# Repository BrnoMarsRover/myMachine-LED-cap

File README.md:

# myMachine-LED-cap
Repository for my Machine LED Cap project, including software, PCBs, and documentation.

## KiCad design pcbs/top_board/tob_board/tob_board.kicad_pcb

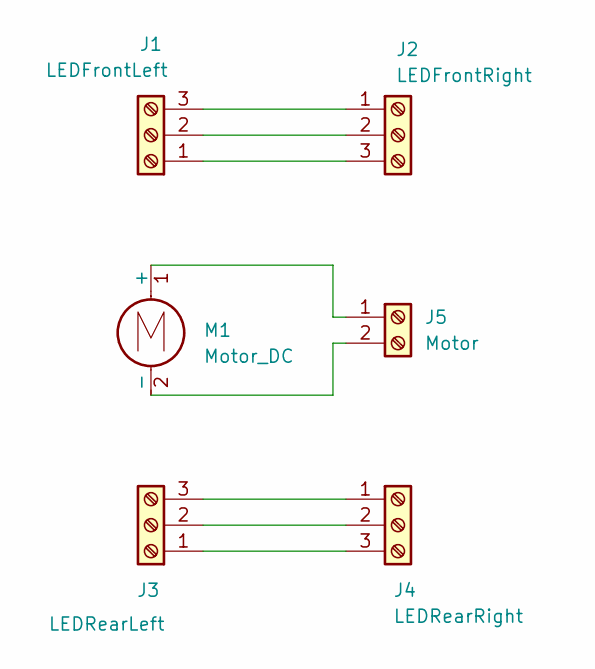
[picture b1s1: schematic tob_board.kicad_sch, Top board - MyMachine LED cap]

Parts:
J1: LEDFrontLeft; JST_XH_S3B-XH-A_1x03_P2.50mm_Horizontal; Manufacturer Part Number S3B-XH-A-1 (LF)(SN)
J2: LEDFrontRight; JST_XH_S3B-XH-A_1x03_P2.50mm_Horizontal; Manufacturer Part Number S3B-XH-A-1 (LF)(SN)
J3: LEDRearLeft; JST_XH_S3B-XH-A_1x03_P2.50mm_Horizontal; Manufacturer Part Number S3B-XH-A-1 (LF)(SN)
J4: LEDRearRight; JST_XH_S3B-XH-A_1x03_P2.50mm_Horizontal; Manufacturer Part Number S3B-XH-A-1 (LF)(SN)
J5: Motor; JST_XH_S2B-XH-A_1x02_P2.50mm_Horizontal; Manufacturer Part Number S2B-XH-A-BK(LF)(SN)
M1: Motor_DC; topMotor; Manufacturer Part Number LA143024A

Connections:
unnamed: J1.1, J2.3
unnamed: J1.2, J2.2
unnamed: J1.3, J2.1
unnamed: J3.1, J4.3
unnamed: J3.2, J4.2
unnamed: J3.3, J4.1
unnamed: J5.1, M1.1 (+)
unnamed: J5.2, M1.2 (-)

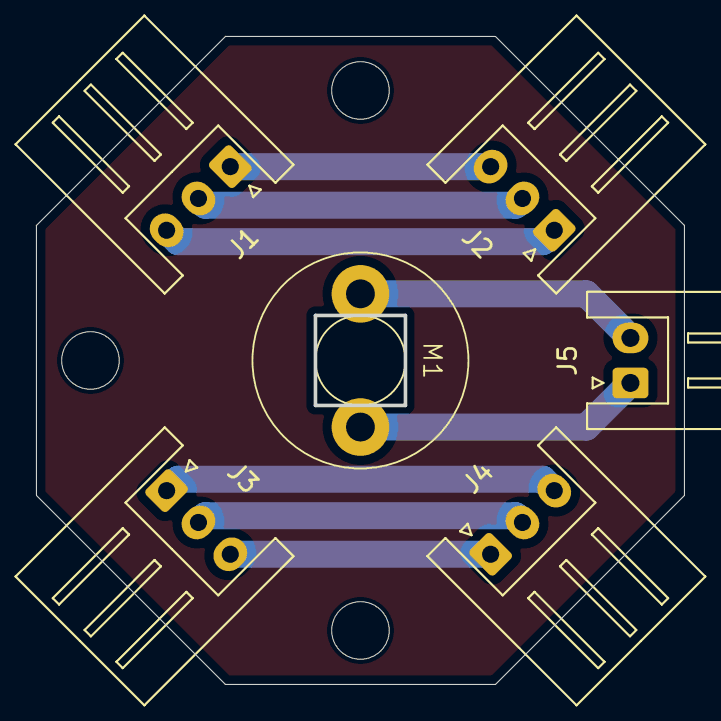
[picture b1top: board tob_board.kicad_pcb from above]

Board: 2 copper layers, 36.0 x 36.0 mm, 6 parts (0 on the bottom side), 8 nets.

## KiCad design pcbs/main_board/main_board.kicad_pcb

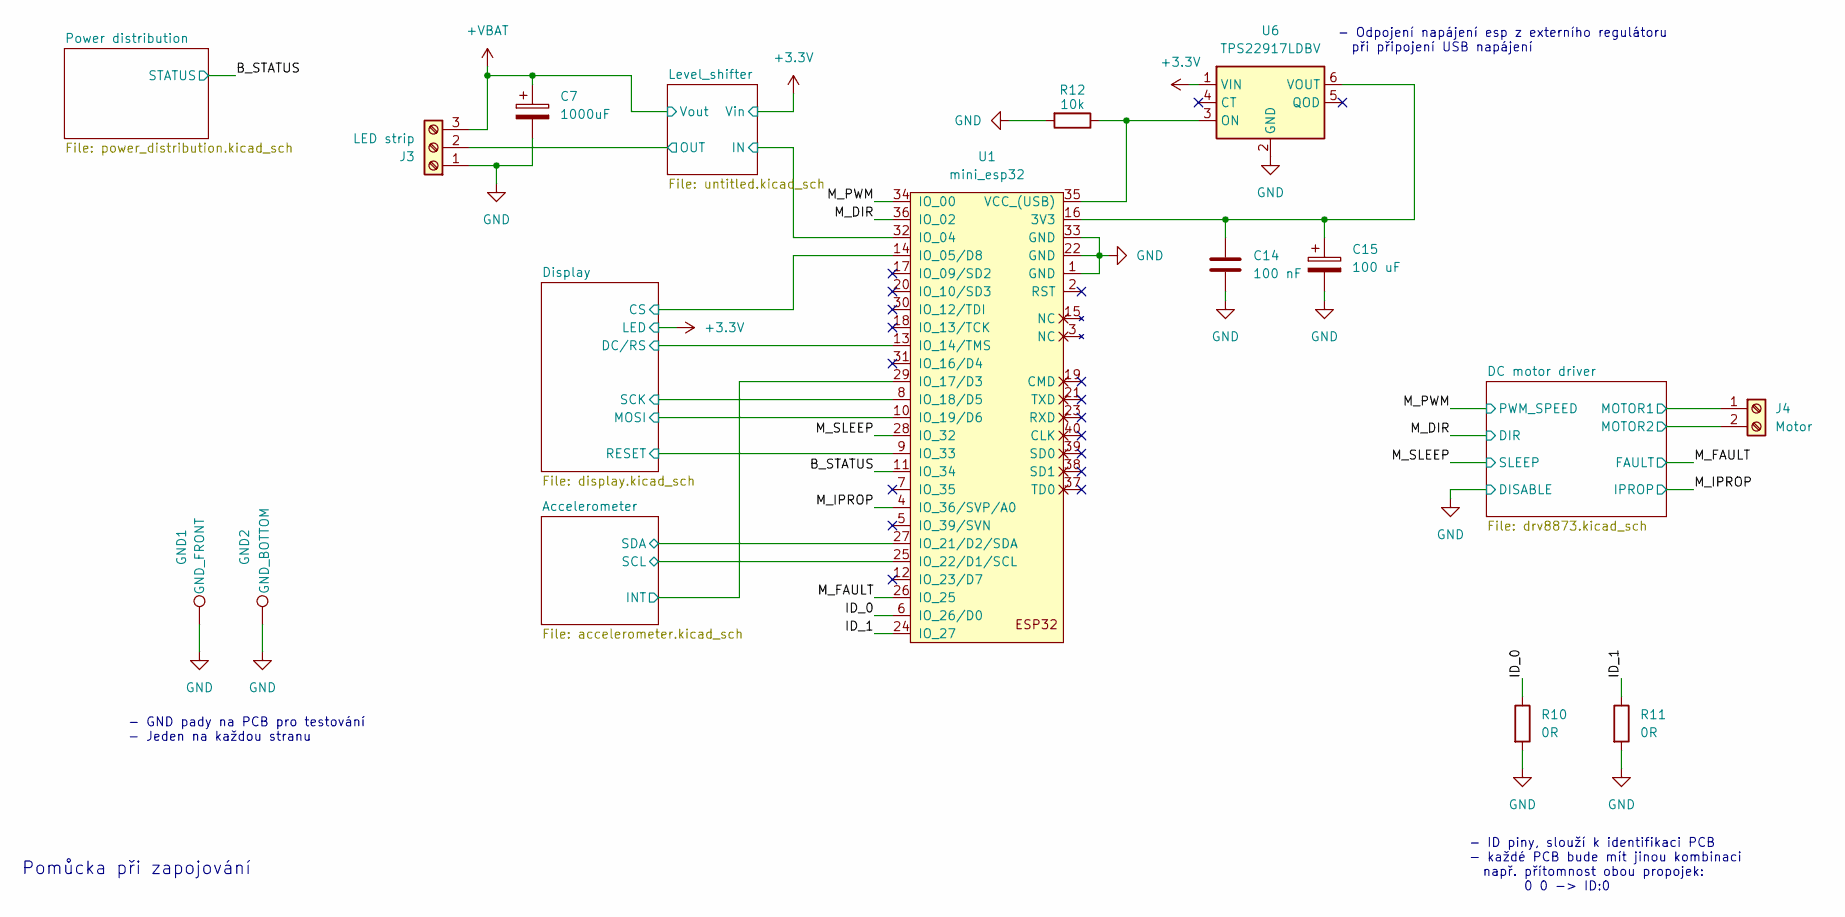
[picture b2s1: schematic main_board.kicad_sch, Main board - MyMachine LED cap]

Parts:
C7: 1000uF; CP_EIA-7360-38_Kemet-E_HandSolder; Manufacturer Part Number TCN4108M006R0055
C14: 100 nF; C_0603_1608Metric_Pad1.08x0.95mm_HandSolder; Manufacturer Part Number C0603C104M5RACTU
C15: 100 uF; CP_EIA-7343-40_Kemet-Y_HandSolder; Manufacturer Part Number T491X107K016AT7280
GND1: GND_FRONT; TestPoint_Pad_1.5x1.5mm
GND2: GND_BOTTOM; TestPoint_Pad_1.5x1.5mm
J3: LED strip; JST_XH_S3B-XH-A-1_1x03_P2.50mm_Horizontal; Manufacturer Part Number S3B-XH-A-1 (LF)(SN)
J4: Motor; JST_XH_S2B-XH-A-1_1x02_P2.50mm_Horizontal; Manufacturer Part Number S2B-XH-A-BK(LF)(SN)
R10, R11: 0R; R_0603_1608Metric_Pad0.98x0.95mm_HandSolder; Manufacturer Part Number CRCW06030000Z0EI
R12: 10k; R_0603_1608Metric_Pad0.98x0.95mm_HandSolder; Manufacturer Part Number CRCW060310K0FKEI
U1: mini_esp32; ESP32_mini; Manufacturer Part Number LA100089
U6: TPS22917LDBV; SOT-23-6; Manufacturer Part Number TPS22917LDBVR

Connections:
+3.3V: U6.1 (VIN); also elsewhere on the board
+VBAT: C7.1, J3.3; also elsewhere on the board
/Accelerometer/INT: U1.29 (IO_17/D3); also elsewhere on the board
/Accelerometer/SCL: U1.25 (IO_22/D1/SCL); also elsewhere on the board
/Accelerometer/SDA: U1.27 (IO_21/D2/SDA); also elsewhere on the board
/B_STATUS: U1.11 (IO_34); also elsewhere on the board
/DC motor driver/MOTOR1: J4.1; also elsewhere on the board
/DC motor driver/MOTOR2: J4.2; also elsewhere on the board
/Display/CS: U1.14 (IO_05/D8); also elsewhere on the board
/Display/DC/RS: U1.13 (IO_14/TMS); also elsewhere on the board
/Display/MOSI: U1.10 (IO_19/D6); also elsewhere on the board
/Display/RESET: U1.9 (IO_33); also elsewhere on the board
/Display/SCK: U1.8 (IO_18/D5); also elsewhere on the board
/ID_0: R10.1, U1.6 (IO_26/D0)
/ID_1: R11.1, U1.24 (IO_27)
/Level_shifter/IN: U1.32 (IO_04); also elsewhere on the board
/Level_shifter/OUT: J3.2; also elsewhere on the board
/M_DIR: U1.36 (IO_02); also elsewhere on the board
/M_FAULT: U1.26 (IO_25); also elsewhere on the board
/M_IPROP: U1.4 (IO_36/SVP/A0); also elsewhere on the board
/M_PWM: U1.34 (IO_00); also elsewhere on the board
/M_SLEEP: U1.28 (IO_32); also elsewhere on the board
GND: C7.2, C14.2, C15.2, GND1.1, GND2.1, J3.1, R10.2, R11.2, R12.2, U1.1 (GND), U1.22 (GND), U1.33 (GND), U6.2 (GND); also elsewhere on the board
unnamed: C14.1, C15.1, U1.16 (3V3), U6.6 (VOUT)
unnamed: R12.1, U1.35 (VCC_(USB)), U6.3 (ON)

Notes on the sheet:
Pomůcka při zapojování
- Odpojení napájení esp z externího regulátoru při připojení USB napájení
- ID piny, slouží k identifikaci PCB - každé PCB bude mít jinou kombinaci např. přítomnost obou propojek: 0 0 -> ID:0
- GND pady na PCB pro testování - Jeden na každou stranu

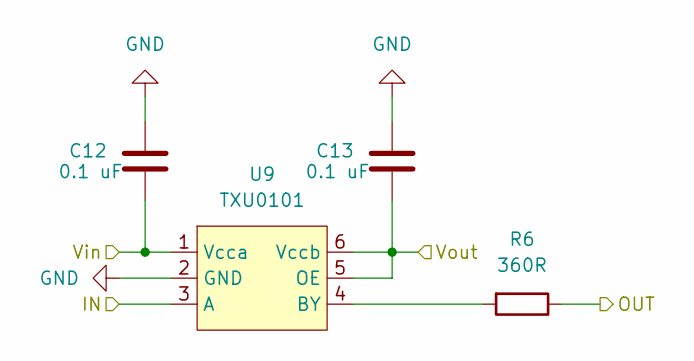
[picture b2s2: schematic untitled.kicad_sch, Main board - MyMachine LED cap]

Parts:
C12, C13: 0.1 uF; C_0603_1608Metric_Pad1.08x0.95mm_HandSolder; Manufacturer Part Number CC0603JRX7R9BB104
R6: 360R; R_0603_1608Metric_Pad0.98x0.95mm_HandSolder; Manufacturer Part Number CRCW0603360RJNTA
U9: TXU0101; SOT-363_SC-70-6_Handsoldering; Manufacturer Part Number TXU0101DCKR

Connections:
+3.3V: C12.1, U9.1 (Vcca); also elsewhere on the board
+VBAT: C13.1, U9.5 (OE), U9.6 (Vccb); also elsewhere on the board
/Level_shifter/IN: U9.3 (A); also elsewhere on the board
/Level_shifter/OUT: R6.1; also elsewhere on the board
GND: C12.2, C13.2, U9.2 (GND); also elsewhere on the board
unnamed: R6.2, U9.4 (BY)

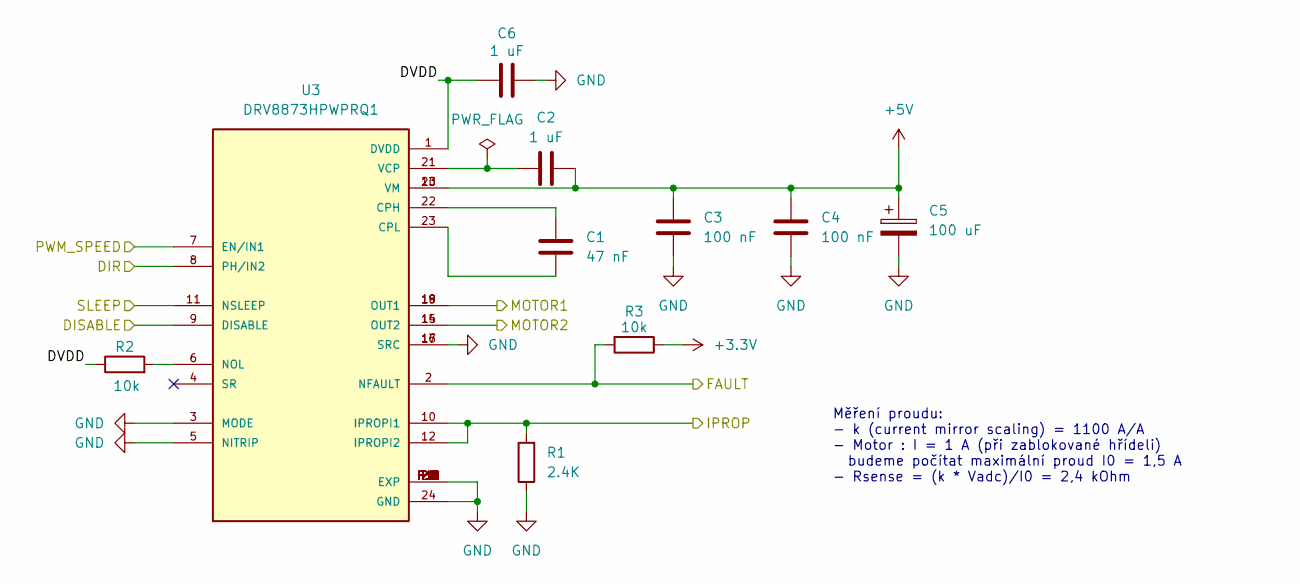
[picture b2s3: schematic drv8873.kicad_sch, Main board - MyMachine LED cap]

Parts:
C1: 47 nF; C_0603_1608Metric_Pad1.08x0.95mm_HandSolder; Manufacturer Part Number CC0603ZRY5V9BB473
C2, C6: 1 uF; C_0603_1608Metric_Pad1.08x0.95mm_HandSolder; Manufacturer Part Number CC0603KRX5R6BB105
C3, C4: 100 nF; C_0603_1608Metric_Pad1.08x0.95mm_HandSolder; Manufacturer Part Number C0603C104M5RACTU
C5: 100 uF; CP_EIA-7343-40_Kemet-Y_HandSolder; Manufacturer Part Number T491X107K016AT7280
R1: 2.4K; R_0603_1608Metric_Pad0.98x0.95mm_HandSolder; Manufacturer Part Number AR0603JR-072K4L
R2, R3: 10k; R_0603_1608Metric_Pad0.98x0.95mm_HandSolder; Manufacturer Part Number CRCW060310K0FKEI
U3: DRV8873HPWPRQ1; SOP65P640X120-25N; Manufacturer Part Number DRV8873HPWPR

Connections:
+3.3V: R3.1; also elsewhere on the board
+5V: C2.2, C3.1, C4.1, C5.1, U3.13 (VM), U3.20 (VM); also elsewhere on the board
/DC motor driver/DVDD: C6.1, R2.1, U3.1 (DVDD)
/DC motor driver/MOTOR1: U3.18 (OUT1), U3.19 (OUT1); also elsewhere on the board
/DC motor driver/MOTOR2: U3.14 (OUT2), U3.15 (OUT2); also elsewhere on the board
/M_DIR: U3.8 (PH/IN2); also elsewhere on the board
/M_FAULT: R3.2, U3.2 (NFAULT); also elsewhere on the board
/M_IPROP: R1.2, U3.10 (IPROPI1), U3.12 (IPROPI2); also elsewhere on the board
/M_PWM: U3.7 (EN/IN1); also elsewhere on the board
/M_SLEEP: U3.11 (NSLEEP); also elsewhere on the board
GND: C3.2, C4.2, C5.2, C6.2, R1.1, U3.3 (MODE), U3.5 (NITRIP), U3.9 (DISABLE), U3.16 (SRC), U3.17 (SRC), U3.24 (GND), U3.25 (EXP), U3.P1 (EXP), U3.P2 (EXP), U3.P3 (EXP), U3.P4 (EXP), U3.P5 (EXP), U3.P6 (EXP), U3.P7 (EXP), U3.P8 (EXP), U3.P9 (EXP), U3.P10 (EXP), U3.P11 (EXP), U3.P12 (EXP), U3.P13 (EXP), U3.P14 (EXP), U3.P15 (EXP), U3.P16 (EXP), U3.P17 (EXP), U3.P18 (EXP); also elsewhere on the board
unnamed: C1.1, U3.22 (CPH)
unnamed: C1.2, U3.23 (CPL)
unnamed: R2.2, U3.6 (NOL)
unnamed: C2.1, U3.21 (VCP)

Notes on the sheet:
Měření proudu: - k (current mirror scaling) = 1100 A/A - Motor : I = 1 A (při zablokované hřídeli) budeme počítat maximální proud I0 = 1,5 A - Rsense = (k * Vadc)/I0 = 2,4 kOhm

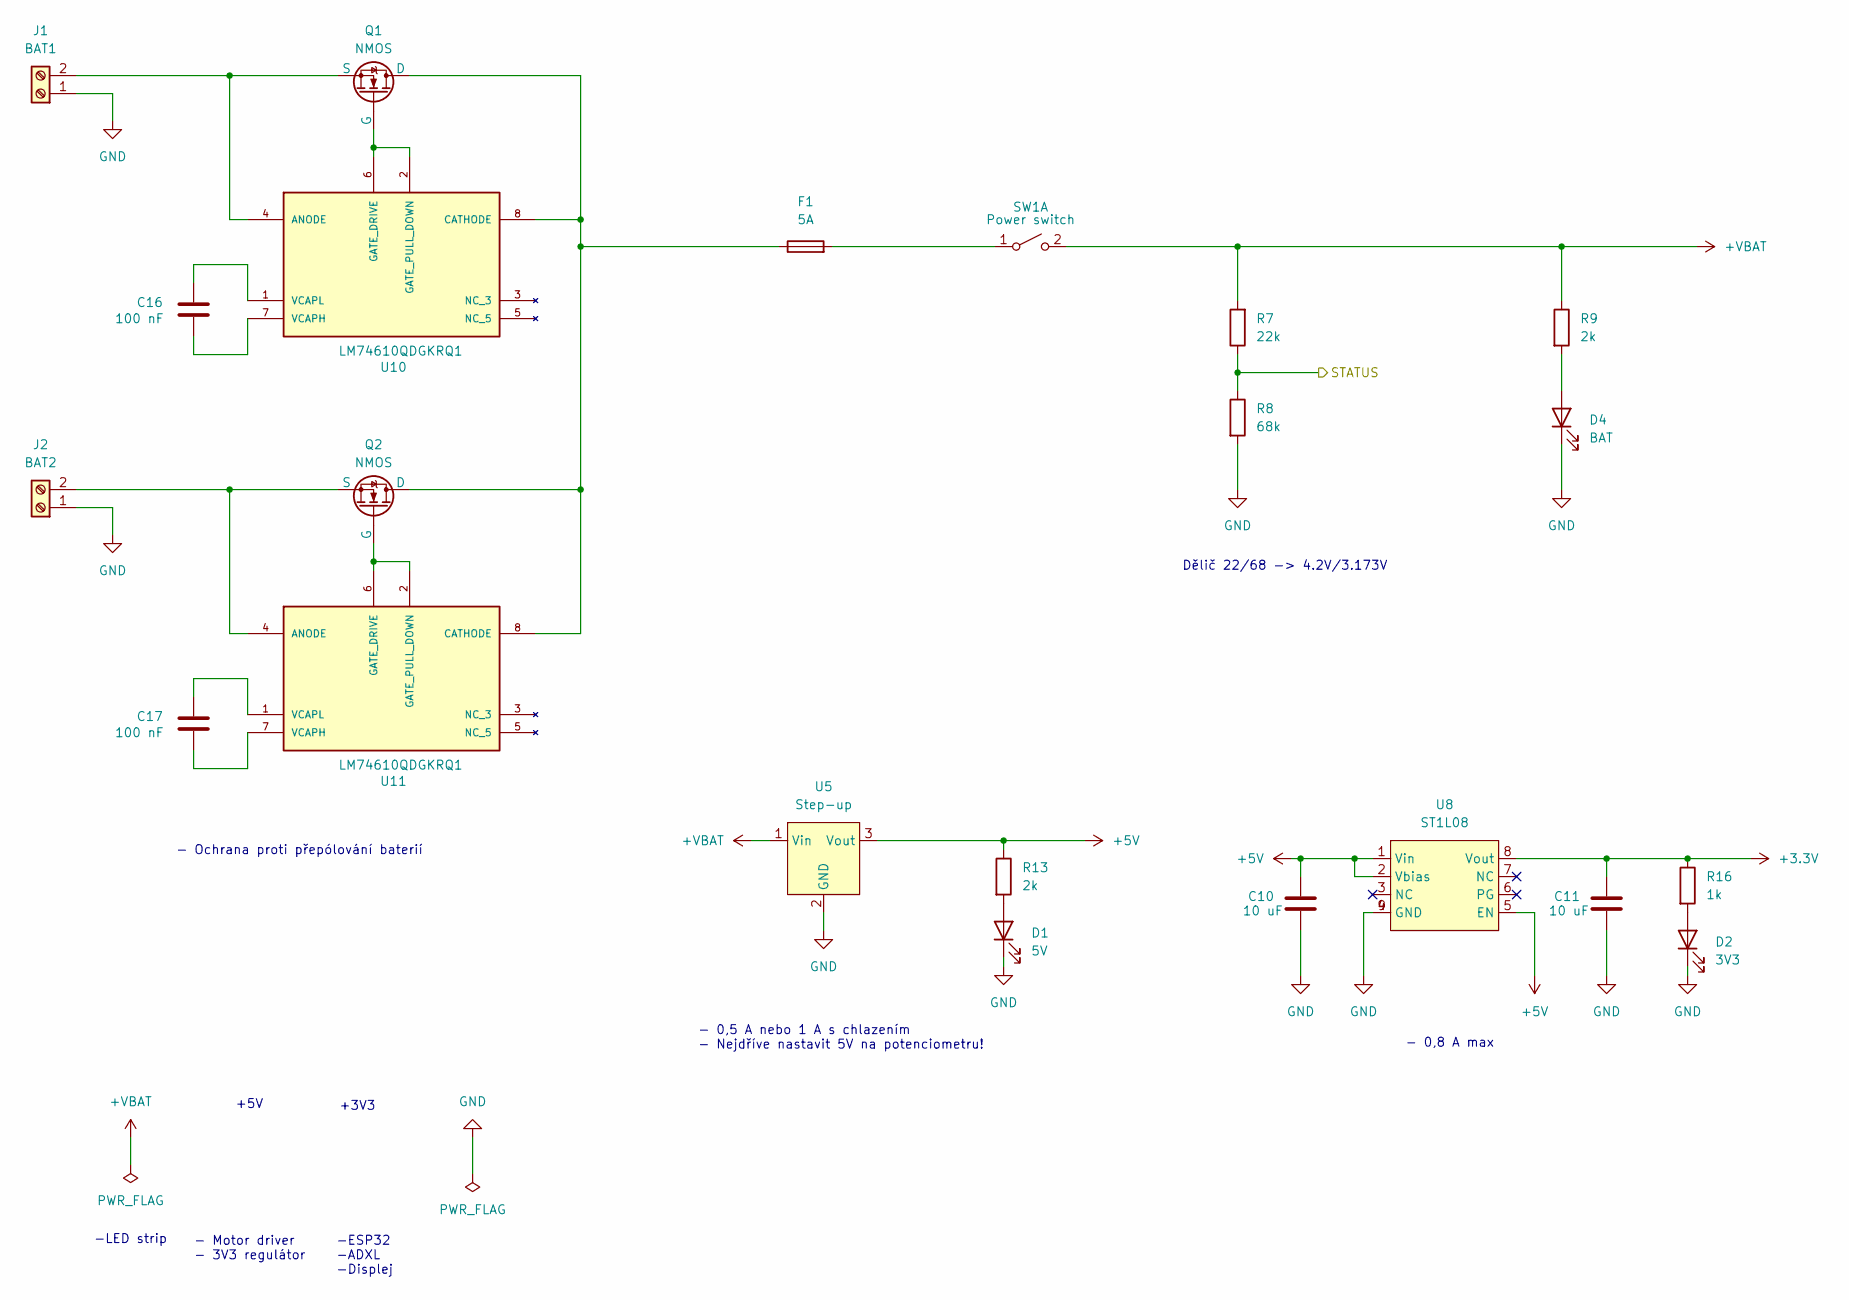
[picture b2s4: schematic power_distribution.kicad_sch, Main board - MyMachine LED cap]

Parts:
C10, C11: 10 uF; C_0603_1608Metric_Pad1.08x0.95mm_HandSolder; Manufacturer Part Number C0603C106M8PAC7411
C16, C17: 100 nF; C_0603_1608Metric_Pad1.08x0.95mm_HandSolder; Manufacturer Part Number C0603C104M5RACTU
D1: 5V; LED_0805_2012Metric_Pad1.15x1.40mm_HandSolder; Manufacturer Part Number APTD2012LCGCK
D2: 3V3; LED_0805_2012Metric_Pad1.15x1.40mm_HandSolder; Manufacturer Part Number APTD2012LCGCK
D4: BAT; LED_0805_2012Metric_Pad1.15x1.40mm_HandSolder; Manufacturer Part Number APTD2012LCGCK
F1: 5A; Fuse_0603_1608Metric_Pad1.05x0.95mm_HandSolder; Manufacturer Part Number SF-0603F500-2
J1: BAT1; JST_XH_S2B-XH-A-1_1x02_P2.50mm_Horizontal; Manufacturer Part Number S2B-XH-A-BK(LF)(SN)
J2: BAT2; JST_XH_S2B-XH-A-1_1x02_P2.50mm_Horizontal; Manufacturer Part Number S2B-XH-A-BK(LF)(SN)
Q1, Q2: NMOS; SO-8_3.9x4.9mm_P1.27mm; Manufacturer Part Number IRF8714TRPBFXTMA1
R7: 22k; R_0603_1608Metric_Pad0.98x0.95mm_HandSolder; Manufacturer Part Number CRCW060322K0FKEBC
R8: 68k; R_0603_1608Metric_Pad0.98x0.95mm_HandSolder; Manufacturer Part Number CRCW060368K0FKTA
R9, R13: 2k; R_0603_1608Metric_Pad0.98x0.95mm_HandSolder; Manufacturer Part Number AR0603FR-072KL
R16: 1k; R_0603_1608Metric_Pad0.98x0.95mm_HandSolder; Manufacturer Part Number RC0603FR-071KL
SW1: Power switch; JST_XH_S2B-XH-A-1_1x02_P2.50mm_Horizontal; Manufacturer Part Number S2B-XH-A-BK(LF)(SN)
U5: Step-up; step-up_module; Manufacturer Part Number LA122015
U8: ST1L08; DFN-8-1EP_3x2mm_P0.5mm_EP1.3x1.5mm; Manufacturer Part Number ST1L08SPU33R
U10, U11: LM74610QDGKRQ1; SOP65P490X110-8N; Manufacturer Part Number LM74610QDGKRQ1

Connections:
+3.3V: C11.2, R16.1, U8.8 (Vout); also elsewhere on the board
+5V: C10.2, R13.1, U5.3 (Vout), U8.1 (Vin), U8.2 (Vbias), U8.5 (EN); also elsewhere on the board
+VBAT: R7.2, R9.1, SW1.2 (B), U5.1 (Vin); also elsewhere on the board
/B_STATUS: R7.1, R8.1; also elsewhere on the board
GND: C10.1, C11.1, D1.1 (K), D2.1 (K), D4.1 (K), J1.1, J2.1, R8.2, U5.2 (GND), U8.4 (GND), U8.9 (GND); also elsewhere on the board
unnamed: D1.2 (A), R13.2
unnamed: D2.2 (A), R16.2
unnamed: D4.2 (A), R9.2
unnamed: J1.2, Q1.1 (S), Q1.2 (S), Q1.3 (S), U10.4 (ANODE)
unnamed: J2.2, Q2.1 (S), Q2.2 (S), Q2.3 (S), U11.4 (ANODE)
unnamed: Q1.4 (G), U10.2 (GATE_PULL_DOWN), U10.6 (GATE_DRIVE)
unnamed: Q2.4 (G), U11.2 (GATE_PULL_DOWN), U11.6 (GATE_DRIVE)
unnamed: F1.2, SW1.1 (A)
unnamed: F1.1, Q1.5 (D), Q1.6 (D), Q1.7 (D), Q1.8 (D), Q2.5 (D), Q2.6 (D), Q2.7 (D), Q2.8 (D), U10.8 (CATHODE), U11.8 (CATHODE)
unnamed: C16.1, U10.7 (VCAPH)
unnamed: C16.2, U10.1 (VCAPL)
unnamed: C17.1, U11.7 (VCAPH)
unnamed: C17.2, U11.1 (VCAPL)

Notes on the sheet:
-ESP32 -ADXL -Displej
-LED strip
+3V3
- Motor driver - 3V3 regulátor
+5V
- 0,8 A max
- 0,5 A nebo 1 A s chlazením - Nejdříve nastavit 5V na potenciometru!
Dělič 22/68 -> 4.2V/3.173V
- Ochrana proti přepólování baterií

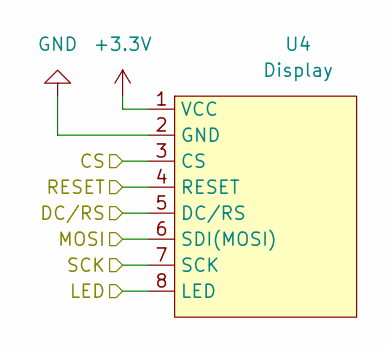
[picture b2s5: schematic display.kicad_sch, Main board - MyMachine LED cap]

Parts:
U4: Display; JST_XH_S8B-XH-A-1_1x08_P2.50mm_Horizontal; Manufacturer Part Number S8B-XH-A-1 (LF)(SN)

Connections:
+3.3V: U4.1 (VCC), U4.8 (LED); also elsewhere on the board
/Display/CS: U4.3 (CS); also elsewhere on the board
/Display/DC/RS: U4.5 (DC/RS); also elsewhere on the board
/Display/MOSI: U4.6 (SDI(MOSI)); also elsewhere on the board
/Display/RESET: U4.4 (RESET); also elsewhere on the board
/Display/SCK: U4.7 (SCK); also elsewhere on the board
GND: U4.2 (GND); also elsewhere on the board

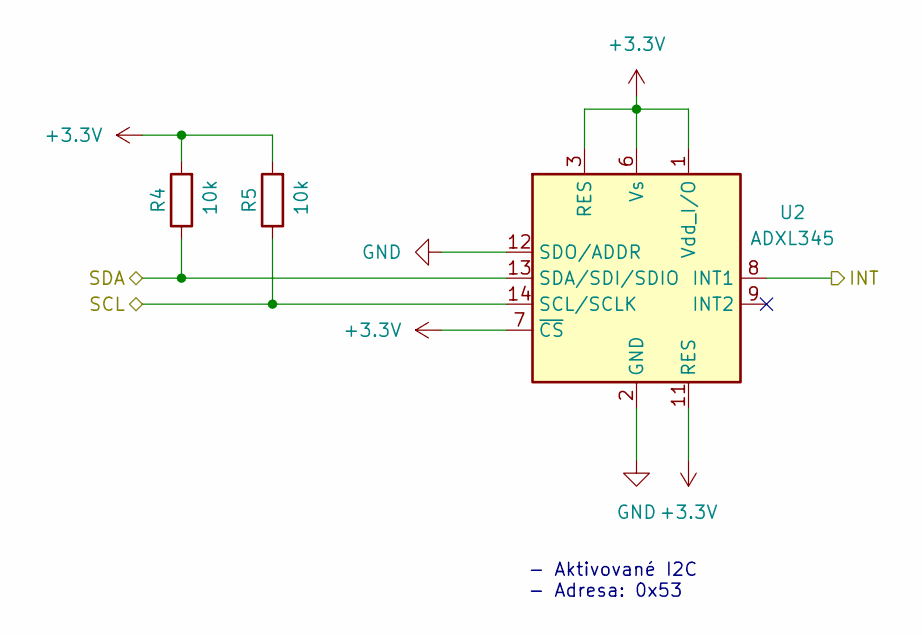
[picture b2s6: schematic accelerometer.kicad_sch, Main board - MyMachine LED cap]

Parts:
R4, R5: 10k; R_0603_1608Metric_Pad0.98x0.95mm_HandSolder; Manufacturer Part Number CRCW060310K0FKEI
U2: ADXL345; LGA-14_3x5mm_P0.8mm_LayoutBorder1x6y; Manufacturer Part Number ADXL345BCCZ

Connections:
+3.3V: R4.2, R5.2, U2.1 (Vdd_I/O), U2.3 (RES), U2.6 (Vs), U2.7 (~CS), U2.11 (RES); also elsewhere on the board
/Accelerometer/INT: U2.8 (INT1); also elsewhere on the board
/Accelerometer/SCL: R5.1, U2.14 (SCL/SCLK); also elsewhere on the board
/Accelerometer/SDA: R4.1, U2.13 (SDA/SDI/SDIO); also elsewhere on the board
GND: U2.2 (GND), U2.4 (GND), U2.5 (GND), U2.12 (SDO/ADDR); also elsewhere on the board

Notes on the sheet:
- Aktivované I2C - Adresa: 0x53

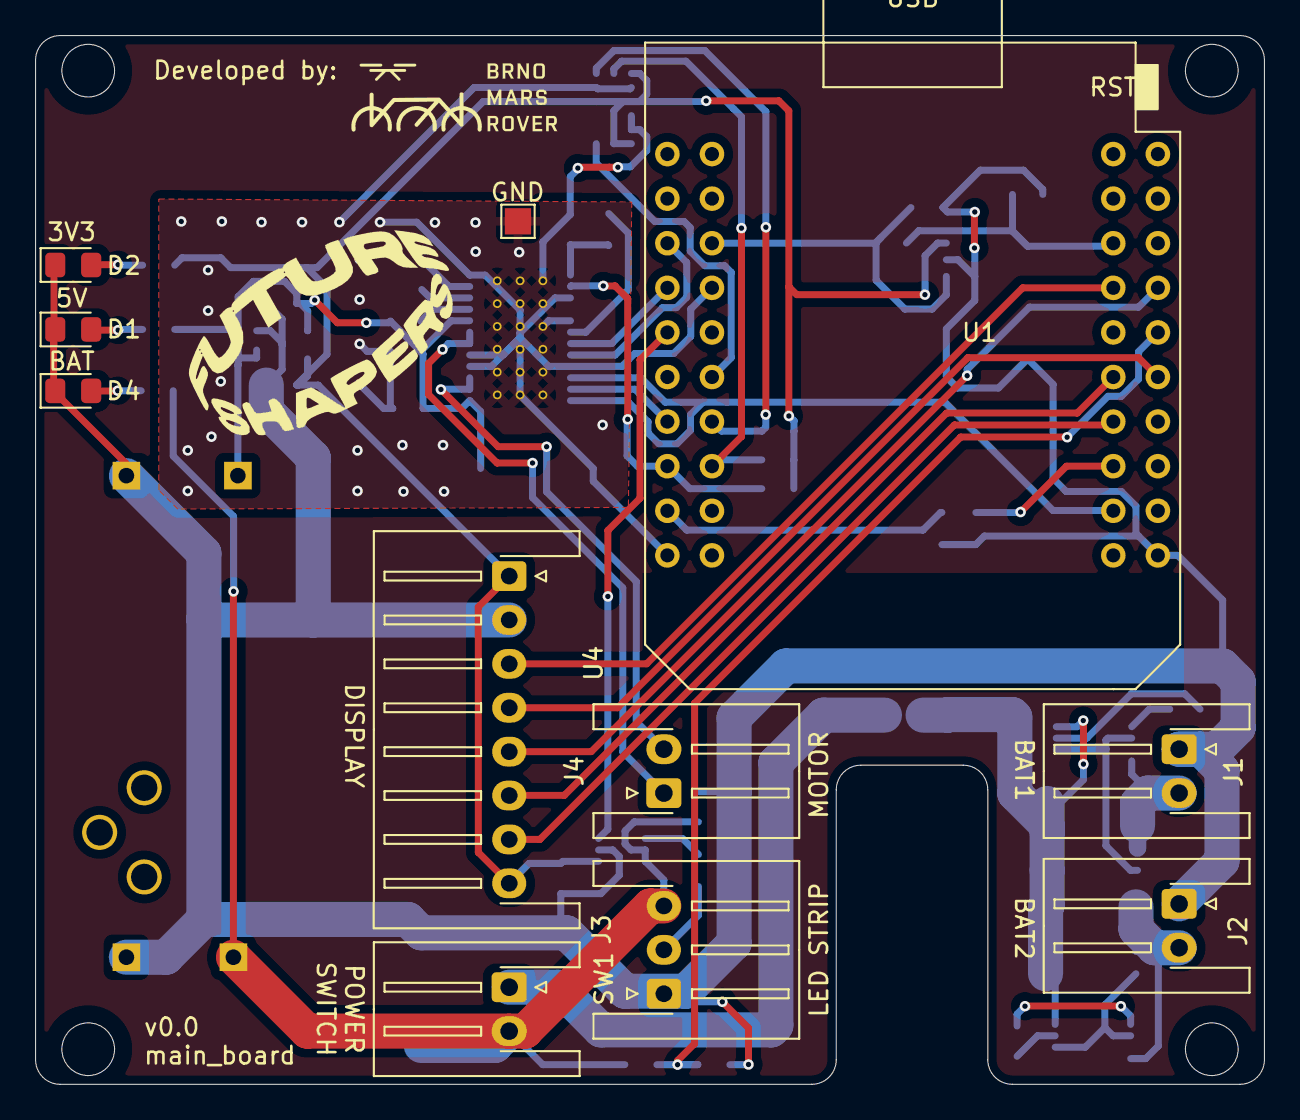
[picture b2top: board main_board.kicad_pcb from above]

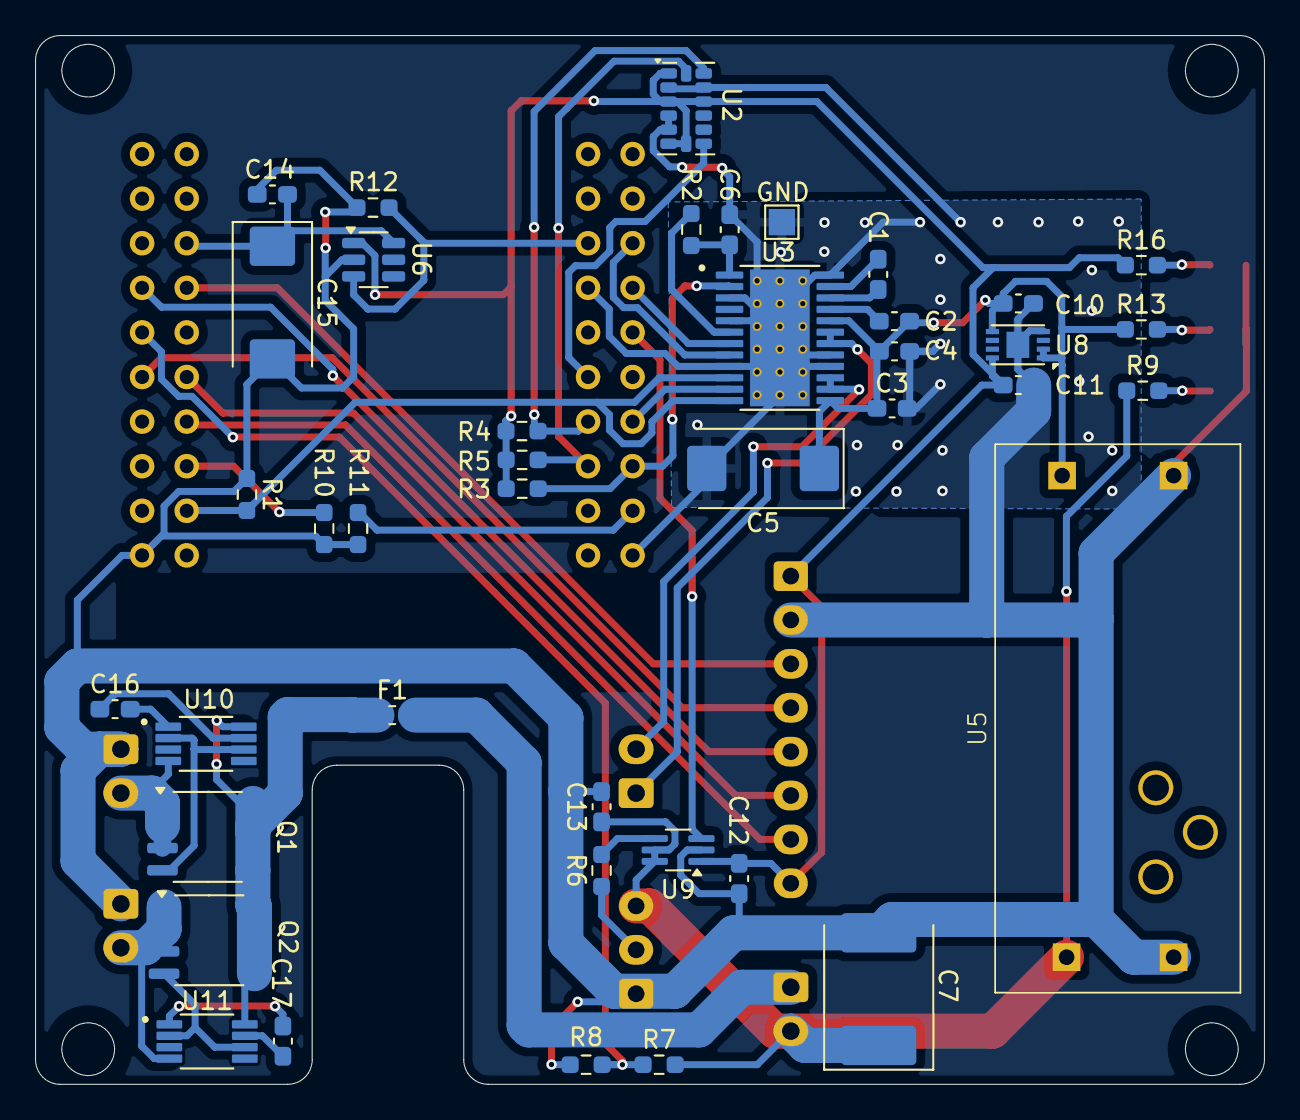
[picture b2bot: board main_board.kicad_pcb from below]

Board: 2 copper layers, 70.0 x 59.7 mm, 56 parts (41 on the bottom side), 45 nets.

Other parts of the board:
H3, H3#2, H3#3, H3#4: MountingHole; MountingHole_3.2mm_M3

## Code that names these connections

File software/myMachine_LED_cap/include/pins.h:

/* =============================================================
 * Project:   myMachine LED Cap
 * File:      pins.h
 * Author:    Martin Kriz
 * Company:   Ullmanna s.r.o.
 * -------------------------------------------------------------
 * Description:
 *   Pin definitions for MH-ET LIVE ESP32 MiniKIT (ESP32-WROOM-32).
 *   Based on pinout.md.
 *
 * Legend:
 *   M_   – DC motor driver (DRV8873H or similar)
 *   D_   – display (SPI)
 *   LED_ – LED strip (WS281x / one-wire data)
 *   A_   – accelerometer (I2C)
 *   B_   – battery
 *   ID_  – hardware identification
 * ============================================================= */

#pragma once

// ── Motor driver ──────────────────────────────────────────────
#define PIN_M_IPROP   36   // ADC1_CH0  – motor current (analog in, ADC1 – Wi-Fi safe)
#define PIN_M_SLEEP   32   // GPIO32    – motor sleep (LOW = sleep)
#define PIN_M_FAULT   25   // GPIO25    – motor fault flag (active LOW)
#define PIN_M_DIR     2    // GPIO2     – motor direction
#define PIN_M_PWM     0    // GPIO0     – motor PWM  ⚠ LOW při bootu = flash mode

// ── Display (SPI) ─────────────────────────────────────────────
#define PIN_D_RESET   33   // GPIO33    – display reset (active LOW)
#define PIN_D_DC      14   // GPIO14    – display data/command (DC/RS)
#define PIN_D_CS      5    // GPIO5     – display chip select (SPI CS)
#define PIN_D_SCK     18   // GPIO18    – display SPI clock (VSPI SCK)
#define PIN_D_MOSI    19   // GPIO19    – display SPI MOSI (VSPI MISO pin, remapped)

// ── LED strip ─────────────────────────────────────────────────
#define PIN_LED_DATA  4    // GPIO4     – LED strip data (WS281x)

// ── Accelerometer (I2C) ───────────────────────────────────────
#define PIN_A_SDA     21   // GPIO21    – I2C SDA
#define PIN_A_SCL     22   // GPIO22    – I2C SCL
#define PIN_A_INT     17   // GPIO17    – accelerometer interrupt

// ── Battery ───────────────────────────────────────────────────
#define PIN_B_STATUS  34   // GPIO34    – battery status (analog in, ADC1 – Wi-Fi safe, input only)

// ── Hardware identification ───────────────────────────────────
#define PIN_ID_0      26   // GPIO26    – HW ID bit 0
#define PIN_ID_1      27   // GPIO27    – HW ID bit 1

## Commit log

2025-11-23 Add first components
2025-12-04 Add example doc
2025-12-04 Add doc template
2025-12-04 Docs fix
2025-12-04 doc update
2025-12-04 Docs update 1
2025-12-04 Docs final init
2025-12-04 Update docs
2025-12-04 Readme update
2025-12-05 Add table of components
2025-12-05 Space for software
2025-12-05 Deployed 0b23063 with MkDocs version: 1.6.1
2025-12-22 Add display footprint, symbol
2025-12-22 Add power distribution sheet
2025-12-23 Add step-up into project
2025-12-23 Display wiring to esp
2025-12-23 Add led strip wiring
2025-12-23 added top board
2025-12-25 wire m driver to esp
2025-12-26 Add files via upload
    update
2025-12-26 Add pinout to docs
2025-12-26 docs update
2025-12-26 Deployed 8eba210 with MkDocs version: 1.6.1
2025-12-27 Add ideal diode
2025-12-28 Add files via upload
    switch and zip update
2025-12-29 board update
2025-12-29 Add reverse polarity protection
2025-12-30 Add connectors
2025-12-30 Changed pinout
2025-12-30 soupky a vožky
2025-12-30 ID pins, BOM, fuse
2025-12-31 navod napsan
2026-01-01 Add big picture
2026-01-01 Hot fix
2026-01-01 Hot fix 2
2026-01-01 Deployed 738139a with MkDocs version: 1.6.1
2026-01-06 Docs review
2026-01-08 small navod update
2026-01-08 návod dokončen
2026-01-08 quick fix
2026-01-08 quick fix 2
2026-01-08 quick fix 3
2026-01-09 ESP power update
2026-01-10 Add IC for charging
2026-01-10 Add 3V3 regulator
2026-01-10 Deployed 34beaa3 with MkDocs version: 1.6.1
2026-01-11 Add edge cuts and notes to pcb
2026-01-12 Add top board BOM
2026-01-14 Change 3V3 regulator, add level shifter for led strip
2026-01-15 Update components list
2026-01-15 Add LED indicators
2026-01-15 Add tmp BOM of main board
2026-01-16 Add docs
2026-01-17 Deployed c53ad77 with MkDocs version: 1.6.1
2026-01-18 fix otaceni a ukladani
2026-01-18 fix otaceni 2
2026-01-18 fix barev
2026-01-19 Components update
2026-01-20 Components upgrade
2026-01-20 Add cap
2026-01-20 Main board final update
2026-01-20 Add schematic of main board
2026-01-20 Add top board schematic
2026-01-21 Add example of web to docs
2026-01-23 changed footprint of level shifter
2026-01-23 Deployed 8f424ba with MkDocs version: 1.6.1
2026-02-09 Main board layout design
2026-02-10 Main_board pcb v0.0
2026-02-10 add gerbers
2026-02-10 Deployed c74815f with MkDocs version: 1.6.1
2026-02-19 Add new ibom for main_board
2026-02-25 Docs step-up info
2026-03-12 Fix bom errors - main board
2026-03-12 thicker connections for easier manufacture
2026-03-12 Deployed ba6a42f with MkDocs version: 1.6.1
2026-03-19 init software project
2026-03-19 Add pins.h
2026-03-19 Add testing code for hw
2026-03-19 oprava pinu
2026-03-19 first version of main code
2026-03-20 Code update
2026-03-20 Add issues after hw testing
2026-03-20 Deployed bc4898d with MkDocs version: 1.6.1
2026-03-22 Add tmp BOM
2026-03-23 Pridani druheho nakupu
2026-03-23 pridani nakupu z feromat
2026-03-23 update druhy nakup
2026-03-25 Add image and bat update
2026-03-26 added accelerometer test data
2026-03-27 Add login page, imu data update
2026-03-27 Pridani jineho policie obrazku, pridani vodorovne cary
2026-03-27 mazani obrazovky pri prepinani modu
2026-03-27 undervoltage protection
2026-03-27 Deployed df90f7d with MkDocs version: 1.6.1
